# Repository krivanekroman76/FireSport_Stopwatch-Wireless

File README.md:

# FireSport Stopwatch Wireless

A DIY wireless stopwatch for FireSport training and running competitions. The system starts timing from a base station and stops when a target sensor or laser gate is triggered on a wireless endpoint, that sends signal back to the base station. It is intended for courses where running long signal cables would be inconvenient, expose them to damage or cables are inconvetions.

> **Project status:** The v6 DIY hardware and firmware are nearing a first full testing version. Timing accuracy, radio range, battery life, and water resistance have not been independently measured or certified. Treat the values and environmental protection described here as design goals, not guarantees.

## System overview

- **Base station:** An ESP32-CAM module, two MAX7219-driven 7-segment displays with 8 digits each, operator buttons, and a buzzer. The displays show the first two lanes; times from lanes 3 and 4 are available to a connected PC.
- **Endpoints:** ESP32-CAM modules with a sensor input and transistor-switched outputs for a 3 W LED and active piezoelectric buzzer. The base assigns each endpoint to a lane and segment.
- **Wireless link:** ESP-NOW, with no router or internet connection required.
- **Sensors:** Magnetic target switches or laser-gate receivers, depending on the course setup. The endpoint firmware is shared across endpoints.
- **Power:** Battery powered; the current design uses 2-cell (2S) Li-ion packs. Battery monitoring and practical runtime testing are still in progress.

The base supports **1–4 lanes**. The current firmware supports **multiple segments (up to 9) for a single lane**; multi-segment timing across several lanes is not currently supported. The physical base display shows two lanes, with additional lane results sent to the PC interface.

## How a run works

1. The operator starts the stopwatch with the base's **START** button.
2. Endpoint sensor events are sent to the base over ESP-NOW. Events are acknowledged and retried until received.
3. The base records the stop time (and segment split times when configured), updates the displays, and reports results over USB serial for PC software.
4. The base's **RESTART** button resets a run. Holding it also displays available battery readings.

The endpoint's LED gives visual feedback when a sensor event is being sent and when it has been acknowledged. Endpoint and base buzzer behavior can be configured at the base.

## V6 DIY hardware

### Base station

The base is not intended to be submerged. Its enclosure is designed to offer some splash resistance, with particular care needed around the three operator buttons, the GX12 connectors (**2-pin START, 3-pin POWER, 5-pin display output**), and the panel-mounted USB-C female connector.

Design reference: [Base and endpoint enclosure](Hardware/Endpoint-BaseBox.pdf)

<!-- Add your v6 photos under photos/DIY-v6/ and update these image paths. -->

[More base photos: all sides and connector details](photos/DIY-v6/base-details/)

### Endpoints

Each endpoint has one sensor input. The magnetic-switch setup is intended for two target lines; laser-gate setups can use one to four lanes, with up to nine segments on a single lane in the current firmware. Assign each endpoint to its lane and segment during base setup.

The endpoint enclosure design is described in the [base and endpoint enclosure document](Hardware/Endpoint-BaseBox.pdf). Protect the GX12 3-pin connections carefully when assembling the endpoint; the enclosure and connectors should not be assumed waterproof.

[More endpoint photos: all sides and connector details](photos/DIY-v6/endpoint-details/)

### Signal box

The separate signal box connects through a GX12 3-pin connector and carries common **+BATT**, a **3 W LED**, and an **active piezoelectric buzzer**. The LED and buzzer need only +BATT and GND at the signal box; they are switched by transistors in the endpoint. The signal box is designed to resist splashing, but its water resistance has not been verified and should not be treated as a waterproof rating.

Design reference: [Signal box](Hardware/SignalBox.pdf)

### System photos

## Firmware

The v6 Arduino sketches are in [`Codes/Hardware_codes/Base_v6`](Codes/Hardware_codes/Base_v6) and [`Codes/Hardware_codes/Endpoint_v6`](Codes/Hardware_codes/Endpoint_v6). Use the matching v6 firmware on the base and every endpoint.

Both sketches use a shared `protocol.h` for ESP-NOW message IDs, event acknowledgements, configuration, and battery messages. The two copies must remain identical. Each sketch also includes a local `config.h` for shared radio settings; provide the same settings to the base and endpoints and do not publish private keys.

The endpoint uses GPIO 16 for its sensor, which conflicts with ESP32-CAM PSRAM; disable PSRAM in the Arduino board settings as noted in the endpoint sketch. GPIO 13 is used for endpoint battery measurement. Because it is an ADC2 pin, measurement requires the radio/Wi-Fi to pause; reliable endpoint battery measurement is still being refined.

The base supports setup and endpoint pairing from its buttons, battery status display, serial commands, and USB serial output for PC integration. See the comments at the top of each sketch for the current pin assignments, setup flow, commands, and serial message formats.

## Wireless range and testing

The intended operating range is approximately **100–1000 m in favorable conditions**, depending on line of sight, interference, antenna placement, and ESP-NOW coverage. This range has not yet been validated in field testing. Relays may be explored in the future for longer courses such as marathons.

Before relying on the stopwatch in a competition, test the complete setup on the intended course. In particular, verify event reception and timing, endpoint assignment, battery readings and runtime, radio range, and enclosure resistance to the expected weather. This is a DIY project and is not a certified timing instrument.

## Project history

The project began with Arduino Nano boards and nRF24L01 radios. It later moved to ESP8266 and ESP-NOW, and then to ESP32-CAM modules to gain more processing speed and usable pins for the evolving design. The v6 base and endpoint firmware use ESP-NOW and the shared `protocol.h` message protocol.

## Contact and customization

Questions, orders, or requests for a specialized configuration can be discussed by email: [krivanekroman76@gmail.com](mailto:krivanekroman76@gmail.com).

## License

See the repository's [LICENSE](LICENSE) for the applicable license terms.

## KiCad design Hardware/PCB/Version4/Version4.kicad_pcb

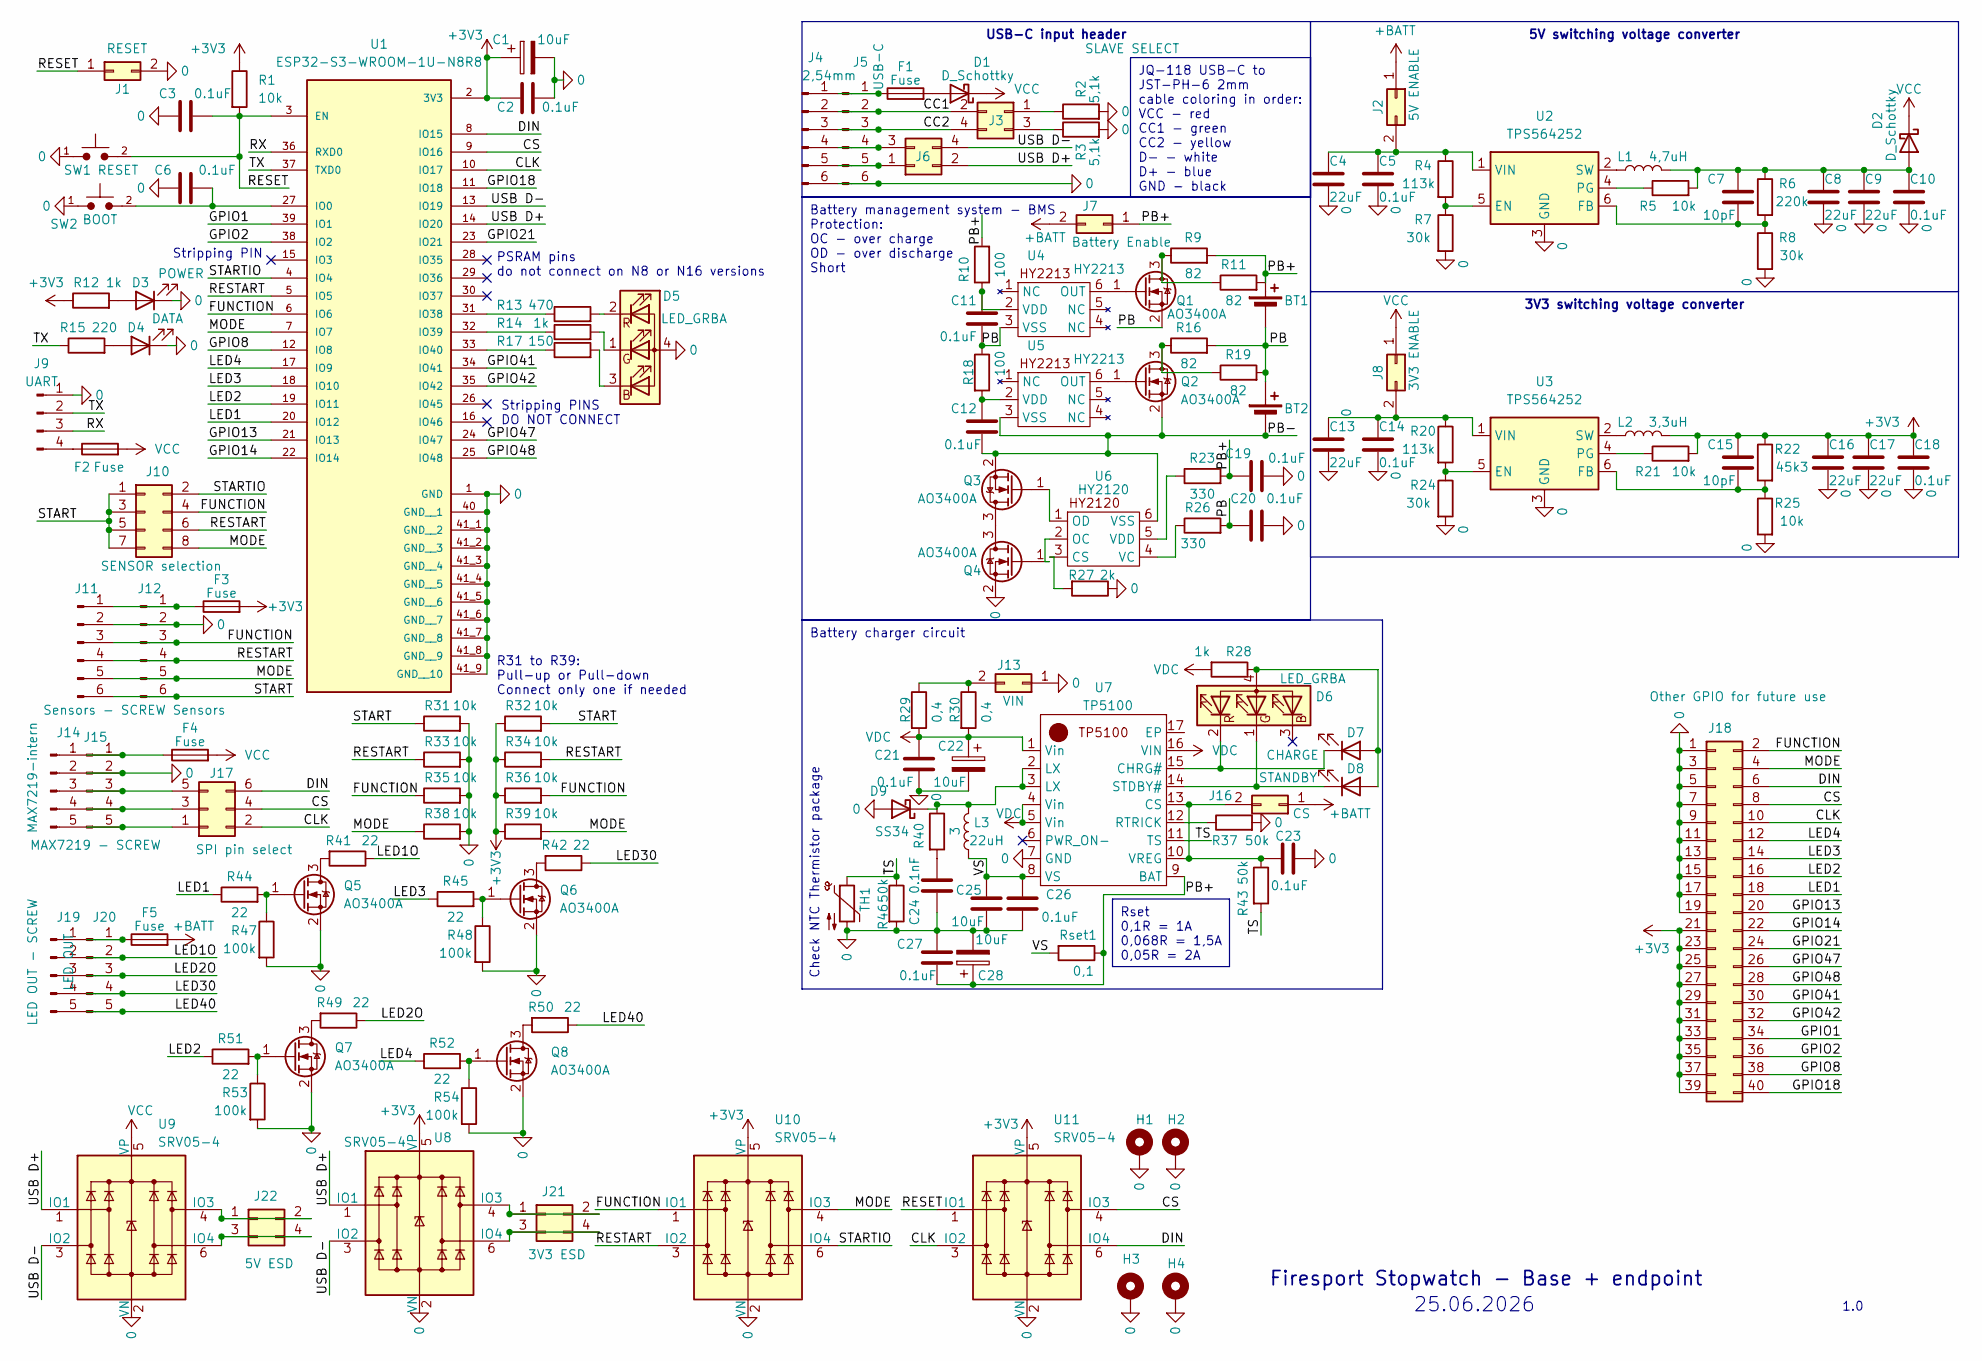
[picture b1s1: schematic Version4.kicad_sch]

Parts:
BT1, BT2: Battery_Cell; BatteryHolder_MPD_BH-18650-PC2
C1, C22, C28: 10uF; CP_Radial_D5.0mm_P2.50mm
C2, C3, C5, C6, C10, C11, C12, C14, C18, C19, C20, C21, C23, C26, C27: 0.1uF; CP_EIA-3216-18_Kemet-A_Pad1.58x1.35mm_HandSolder
C4, C8, C9, C13, C16, C17: 22uF; CP_EIA-3216-18_Kemet-A_Pad1.58x1.35mm_HandSolder
C7, C15: 10pF; CP_EIA-3216-18_Kemet-A_Pad1.58x1.35mm_HandSolder
C24: 0.1nF; CP_EIA-3216-18_Kemet-A_Pad1.58x1.35mm_HandSolder
C25: 10uF; CP_EIA-3216-18_Kemet-A_Pad1.58x1.35mm_HandSolder
D1, D2: D_Schottky; D_SMA_Handsoldering
D3: POWER; LED_1206_3216Metric_Pad1.42x1.75mm_HandSolder
D4: DATA; LED_1206_3216Metric_Pad1.42x1.75mm_HandSolder
D5, D6: LED_GRBA; LED_D5.0mm-4_RGB_Wide_Pins
D7: CHARGE; LED_1206_3216Metric_Pad1.42x1.75mm_HandSolder
D8: STANDBY; LED_1206_3216Metric_Pad1.42x1.75mm_HandSolder
D9: SS34; D_SMA
F1, F2, F3, F4, F5: Fuse; Fuse_1206_3216Metric_Pad1.42x1.75mm_HandSolder
H1, H2, H3, H4: MountingHole_Pad; MountingHole_3.2mm_M3_DIN965_Pad_TopBottom
J1: RESET; PinHeader_2x01_P2.54mm_Vertical
J2: 5V ENABLE; PinHeader_2x01_P2.54mm_Vertical
J3: SLAVE SELECT; PinHeader_2x02_P2.54mm_Vertical
J4: 2,54mm; PinHeader_1x06_P2.54mm_Vertical
J5: USB-C; JST_PH_B6B-PH-K_1x06_P2.00mm_Vertical
J6: USB data lines; PinHeader_2x02_P2.54mm_Vertical
J7: Battery Enable; PinHeader_2x01_P2.54mm_Vertical
J8: 3V3 ENABLE; PinHeader_2x01_P2.54mm_Vertical
J9: UART; PinHeader_1x04_P2.54mm_Vertical
J10: SENSOR selection; PinHeader_2x04_P2.54mm_Vertical
J11: Sensors - SCREW; TerminalBlock_bornier-6_P5.08mm
J12: Sensors; PinHeader_1x06_P2.54mm_Vertical
J13: VIN; PinHeader_2x01_P2.54mm_Vertical
J14: MAX7219-intern; PinHeader_1x05_P2.54mm_Vertical
J15: MAX7219 - SCREW; TerminalBlock_bornier-5_P5.08mm
J16: CS; PinHeader_2x01_P2.54mm_Vertical
J17: SPI pin select; PinHeader_2x03_P2.54mm_Vertical
J18: Other GPIO for future use; PinHeader_2x20_P2.54mm_Vertical
J19: LED OUT - SCREW; TerminalBlock_bornier-5_P5.08mm
J20: LED OUT; PinHeader_1x05_P2.54mm_Vertical
J21: 3V3 ESD; PinHeader_2x02_P2.54mm_Vertical
J22: 5V ESD; PinHeader_2x02_P2.54mm_Vertical
L1: 4,7uH; L_7.3x7.3_H3.5
L2: 3,3uH; L_10.4x10.4_H4.8
L3: 22uH; L_7.3x7.3_H3.5
Q1, Q2, Q3, Q4, Q5, Q6, Q7, Q8: AO3400A; SOT-23
R1, R5, R21, R25, R31, R32, R33, R34, R35, R36, R38, R39: 10k; R_1206_3216Metric_Pad1.30x1.75mm_HandSolder
R2, R3: 5,1k; R_1206_3216Metric_Pad1.30x1.75mm_HandSolder
R4, R20: 113k; R_1206_3216Metric_Pad1.30x1.75mm_HandSolder
R6: 220k; R_1206_3216Metric_Pad1.30x1.75mm_HandSolder
R7, R8, R24: 30k; R_1206_3216Metric_Pad1.30x1.75mm_HandSolder
R9, R11, R16, R19: 82; R_1206_3216Metric_Pad1.30x1.75mm_HandSolder
R10, R18: 100; R_1206_3216Metric_Pad1.30x1.75mm_HandSolder
R12, R14, R28: 1k; R_1206_3216Metric_Pad1.30x1.75mm_HandSolder
R13: 470; R_1206_3216Metric_Pad1.30x1.75mm_HandSolder
R15: 220; R_1206_3216Metric_Pad1.30x1.75mm_HandSolder
R17: 150; R_1206_3216Metric_Pad1.30x1.75mm_HandSolder
R22: 45k3; R_1206_3216Metric_Pad1.30x1.75mm_HandSolder
R23, R26: 330; R_1206_3216Metric_Pad1.30x1.75mm_HandSolder
R27: 2k; R_1206_3216Metric_Pad1.30x1.75mm_HandSolder
R29, R30: 0,4; R_1206_3216Metric_Pad1.30x1.75mm_HandSolder
R37, R43, R46: 50k; R_1206_3216Metric_Pad1.30x1.75mm_HandSolder
R40: 3; R_1206_3216Metric_Pad1.30x1.75mm_HandSolder
R41, R42, R44, R45, R49, R50, R51, R52: 22; R_1206_3216Metric_Pad1.30x1.75mm_HandSolder
R47, R48, R53, R54: 100k; R_1206_3216Metric_Pad1.30x1.75mm_HandSolder
Rset1: 0,1; R_1206_3216Metric_Pad1.30x1.75mm_HandSolder
SW1: RESET; SW_Tactile_SPST_NO_Straight_CK_PTS636Sx25SMTRLFS
SW2: BOOT; SW_Tactile_SPST_NO_Straight_CK_PTS636Sx25SMTRLFS
TH1: Thermistor_NTC; PinHeader_1x02_P2.54mm_Vertical
U1: ESP32-S3-WROOM-1U-N8R8; XCVR_ESP32-S3-WROOM-1U-N8R8; PARTREV v1.1
U2, U3: TPS564252; SOT-23-6_Handsoldering
U4, U5: HY2213; SOT-23-6_Handsoldering
U6: HY2120; SOT-23-6_Handsoldering
U7: TP5100; QFN-16-1EP_5x5mm_P0.8mm_EP2.7x2.7mm
U8, U9, U10, U11: SRV05-4; SOT-23-6

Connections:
0: C1.2, C2.2, C3.1, C4.1, C5.1, C6.1, C8.1, C9.1, C10.1, C13.1, C14.1, C16.1, C17.1, C18.1, C19.1, C20.2, C21.2, C22.2, C23.2, C24.1, C25.1, C26.1, C27.1, C28.2, D3.1 (K), D4.1 (K), D5.4 (A), D9.2 (A), H1.1, H2.1, H3.1, H4.1, J1.2, J4.6, J5.6, J9.1, J11.2, J12.2, J13.1, J14.2, J15.2, J18.1, J18.3, J18.5, J18.7, J18.9, J18.11, J18.13, J18.15, J18.17, J18.19, Q4.2 (S), Q5.2 (S), Q6.2 (S), Q7.2 (S), Q8.2 (S), R2.2, R3.2, R7.2, R8.2, R24.2, R25.2, R27.1, R31.2, R33.2, R35.2, R37.2, R38.2, R46.2, R47.2, R48.2, R53.2, R54.2, SW1.1, SW2.1, TH1.2, U1.1 (GND), U1.40 (GND__1), U1.41_1 (GND__2), U1.41_2 (GND__3), U1.41_3 (GND__4), U1.41_4 (GND__5), U1.41_5 (GND__6), U1.41_6 (GND__7), U1.41_7 (GND__8), U1.41_8 (GND__9), U1.41_9 (GND__10), U2.3 (GND), U3.3 (GND), U7.7 (GND), U8.2 (VN), U9.2 (VN), U10.2 (VN), U11.2 (VN)
+3V3: C1.1, C2.1, C15.2, C16.2, C17.2, C18.2, F3.2, J18.21, J18.23, J18.25, J18.27, J18.29, J18.31, J18.33, J18.35, J18.37, J18.39, L2.1, R1.1, R12.1, R21.2, R22.1, R32.1, R34.1, R36.1, R39.1, U1.2 (3V3), U8.5 (VP), U10.5 (VP), U11.5 (VP)
+BATT: F5.2, J2.1, J7.2, J16.1
/CC1: J3.2, J4.2, J5.2
/CC2: J3.4, J4.3, J5.3
/CLK: J17.2, J18.10, U1.10 (IO17), U11.3 (IO2)
/CS: J17.4, J18.8, U1.9 (IO16), U11.4 (IO3)
/DIN: J17.6, J18.6, U1.8 (IO15), U11.6 (IO4)
/FUNCTION: J10.4, J11.3, J12.3, J18.2, R35.1, R36.2, U1.6 (IO6), U10.1 (IO1)
/GPIO1: J18.34, U1.39 (IO1)
/GPIO2: J18.36, U1.38 (IO2)
/GPIO8: J18.38, U1.12 (IO8)
/GPIO13: J18.20, U1.21 (IO13)
/GPIO14: J18.22, U1.22 (IO14)
/GPIO18: J18.40, U1.11 (IO18)
/GPIO21: J18.24, U1.23 (IO21)
/GPIO41: J18.30, U1.34 (IO41)
/GPIO42: J18.32, U1.35 (IO42)
/GPIO47: J18.26, U1.24 (IO47)
/GPIO48: J18.28, U1.25 (IO48)
/LED1: J18.18, R44.1, U1.20 (IO12)
/LED1O: J19.2, J20.2, R41.1
/LED2: J18.16, R51.1, U1.19 (IO11)
/LED2O: J19.3, J20.3, R49.1
/LED3: J18.14, R45.1, U1.18 (IO10)
/LED4: J18.12, R52.1, U1.17 (IO9)
/LED30: J19.4, J20.4, R42.1
/LED40: J19.5, J20.5, R50.1
/MODE: J10.8, J11.5, J12.5, J18.4, R38.1, R39.2, U1.7 (IO7), U10.4 (IO3)
/PB: BT1.2 (-), BT2.1 (+), C11.2, C20.1, Q1.2 (S), R16.2, R18.1, R19.2, R26.2, U4.3 (VSS)
/PB+: BT1.1 (+), C19.2, C27.2, C28.1, J7.1, R9.2, R10.2, R11.2, R23.2, Rset1.1, U7.9 (BAT)
/PB-: BT2.2 (-), C12.2, Q2.2 (S), Q3.2 (S), U5.3 (VSS), U6.6 (VSS)
/RESET: C3.2, J1.1, R1.2, SW1.2, U1.3 (EN), U11.1 (IO1)
/RESTART: J10.6, J11.4, J12.4, R33.1, R34.2, U1.5 (IO5), U10.3 (IO2)
/RX: J9.3, U1.36 (RXD0)
/START: J10.1, J10.3, J10.5, J10.7, J11.6, J12.6, R31.1, R32.2
/STARTIO: J10.2, U1.4 (IO4), U10.6 (IO4)
/TS: R43.2, R46.1, TH1.1, U7.11 (TS)
/TX: J9.2, R15.1, U1.37 (TXD0)
/USB D+: J6.2, U1.14 (IO20), U8.1 (IO1), U9.1 (IO1)
/USB D-: J6.4, U1.13 (IO19), U8.3 (IO2), U9.3 (IO2)
/VS: C25.2, C26.2, L3.1, Rset1.2, U7.8 (VS)
unnamed: C24.2, R40.2
unnamed: D1.2 (A), F1.2
unnamed: C7.2, C8.2, C9.2, C10.2, D2.2 (A), L1.1, R5.2, R6.1
unnamed: D3.2 (A), R12.2
unnamed: D4.2 (A), R15.2
unnamed: D5.3 (BK), R17.2
unnamed: D5.1 (GK), R14.2
unnamed: D5.2 (RK), R13.2
unnamed: D6.4 (A), D7.2 (A), D8.2 (A), R28.1
unnamed: D6.1 (GK), D8.1 (K), U7.14 (STDBY#)
unnamed: D6.2 (RK), D7.1 (K), U7.15 (CHRG#)
unnamed: D9.1 (K), L3.2, R40.1, U7.2 (LX), U7.3 (LX)
unnamed: C4.2, C5.2, J2.2, R4.1, U2.1 (VIN)
unnamed: J3.1, R2.1
unnamed: J3.3, R3.1
unnamed: F1.1, J4.1, J5.1
unnamed: J4.4, J5.4, J6.3
unnamed: J4.5, J5.5, J6.1
unnamed: C13.2, C14.2, J8.2, R20.1, U3.1 (VIN)
unnamed: F2.1, J9.4
unnamed: F3.1, J11.1, J12.1
unnamed: J13.2, R29.1, R30.1
unnamed: F4.1, J14.1, J15.1
unnamed: J14.3, J15.3, J17.5
unnamed: J14.4, J15.4, J17.3
unnamed: J14.5, J15.5, J17.1
unnamed: C23.1, J16.2, R43.1, U7.10 (VREG), U7.13 (CS)
unnamed: F5.1, J19.1, J20.1
unnamed: J21.1, J21.2, U8.4 (IO3)
unnamed: J21.3, J21.4, U8.6 (IO4)
unnamed: J22.1, J22.2, U9.4 (IO3)
unnamed: J22.3, J22.4, U9.6 (IO4)
unnamed: Q1.3 (D), R9.1, R11.1
unnamed: Q1.1 (G), U4.6 (OUT)
unnamed: Q2.3 (D), R16.1, R19.1
unnamed: Q2.1 (G), U5.6 (OUT)
unnamed: Q3.3 (D), Q4.3 (D)
unnamed: Q3.1 (G), U6.1 (OD)
unnamed: Q4.1 (G), U6.2 (OC)
unnamed: Q5.3 (D), R41.2
unnamed: Q5.1 (G), R44.2, R47.1
unnamed: Q6.3 (D), R42.2
unnamed: Q6.1 (G), R45.2, R48.1
unnamed: Q7.3 (D), R49.2
unnamed: Q7.1 (G), R51.2, R53.1
unnamed: Q8.3 (D), R50.2
unnamed: Q8.1 (G), R52.2, R54.1
unnamed: C6.2, SW2.2, U1.27 (IO0)
unnamed: R13.1, U1.31 (IO38)
unnamed: R14.1, U1.32 (IO39)
unnamed: R17.1, U1.33 (IO40)
unnamed: R4.2, R7.1, U2.5 (EN)
unnamed: C7.1, R6.2, R8.1, U2.6 (FB)
unnamed: R5.1, U2.4 (PG)
unnamed: L1.2, U2.2 (SW)
unnamed: R20.2, R24.1, U3.5 (EN)
unnamed: C15.1, R22.2, R25.1, U3.6 (FB)
unnamed: R21.1, U3.4 (PG)
unnamed: L2.2, U3.2 (SW)
unnamed: C11.1, R10.1, U4.2 (VDD)
unnamed: C12.1, R18.2, U5.2 (VDD)
unnamed: R27.2, U6.3 (CS)
unnamed: R26.1, U6.4 (VC)
unnamed: R23.1, U6.5 (VDD)
unnamed: R37.1, U7.12 (RTRICK)
VCC: D1.1 (K), D2.1 (K), F2.2, F4.2, J8.1, U9.5 (VP)
VDC: C21.1, C22.1, R28.2, R29.2, R30.2, U7.1 (Vin), U7.4 (Vin), U7.5 (Vin), U7.16 (VIN)

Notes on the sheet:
5V switching voltage converter
USB-C input header
JQ-118 USB-C to JST-PH-6 2mm cable coloring in order: VCC - red CC1 - green CC2 - yellow D- - white D+ - blue GND - black
3V3 switching voltage converter
Battery management system - BMS Protection: OC - over charge OD - over discharge Short
Rset 0,1R = 1A 0,068R = 1,5A 0,05R = 2A
Battery charger circuit
25.06.2026
Firesport Stopwatch - Base + endpoint
Stripping PIN
1.0
R31 to R39: Pull-up or Pull-down Connect only one if needed
PSRAM pins do not connect on N8 or N16 versions
Check NTC Thermistor package
Stripping PINS DO NOT CONNECT

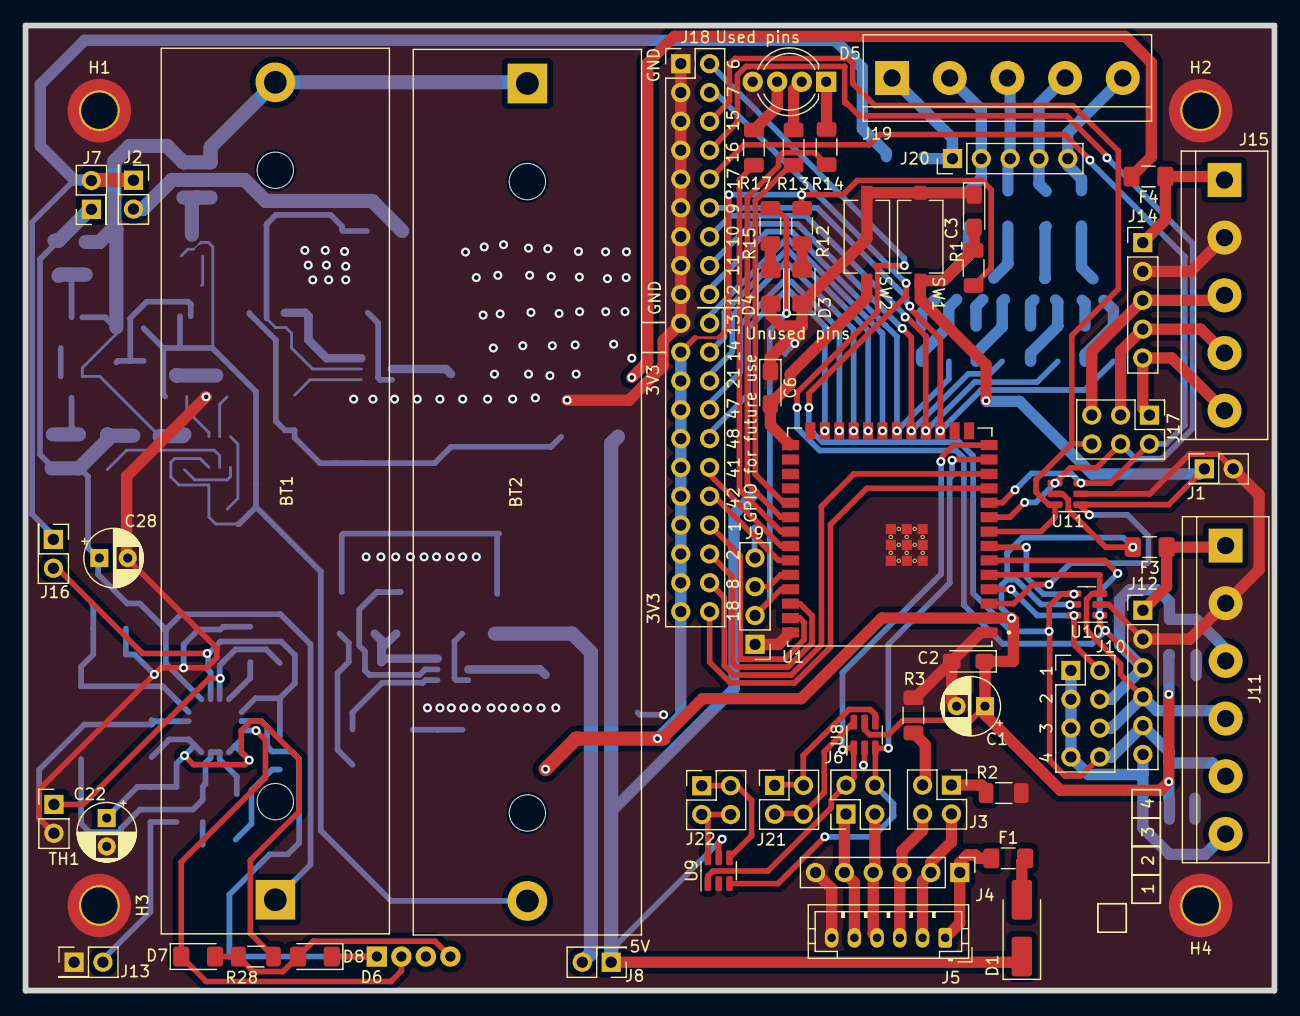
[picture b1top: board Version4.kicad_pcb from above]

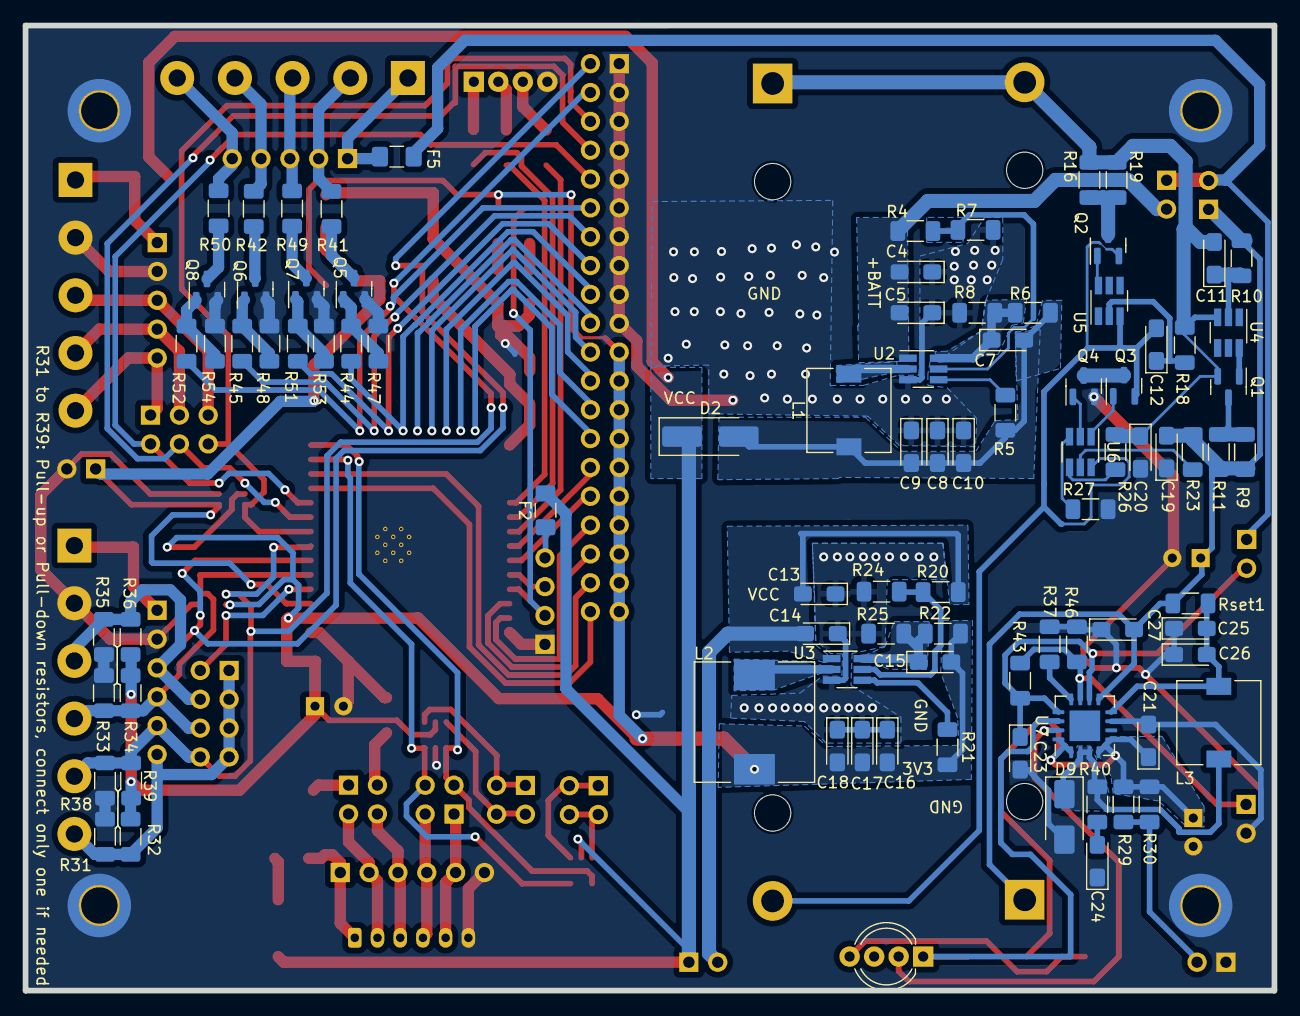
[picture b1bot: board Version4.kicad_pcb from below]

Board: 2 copper layers, 110.0 x 85.0 mm, 150 parts (90 on the bottom side), 109 nets.

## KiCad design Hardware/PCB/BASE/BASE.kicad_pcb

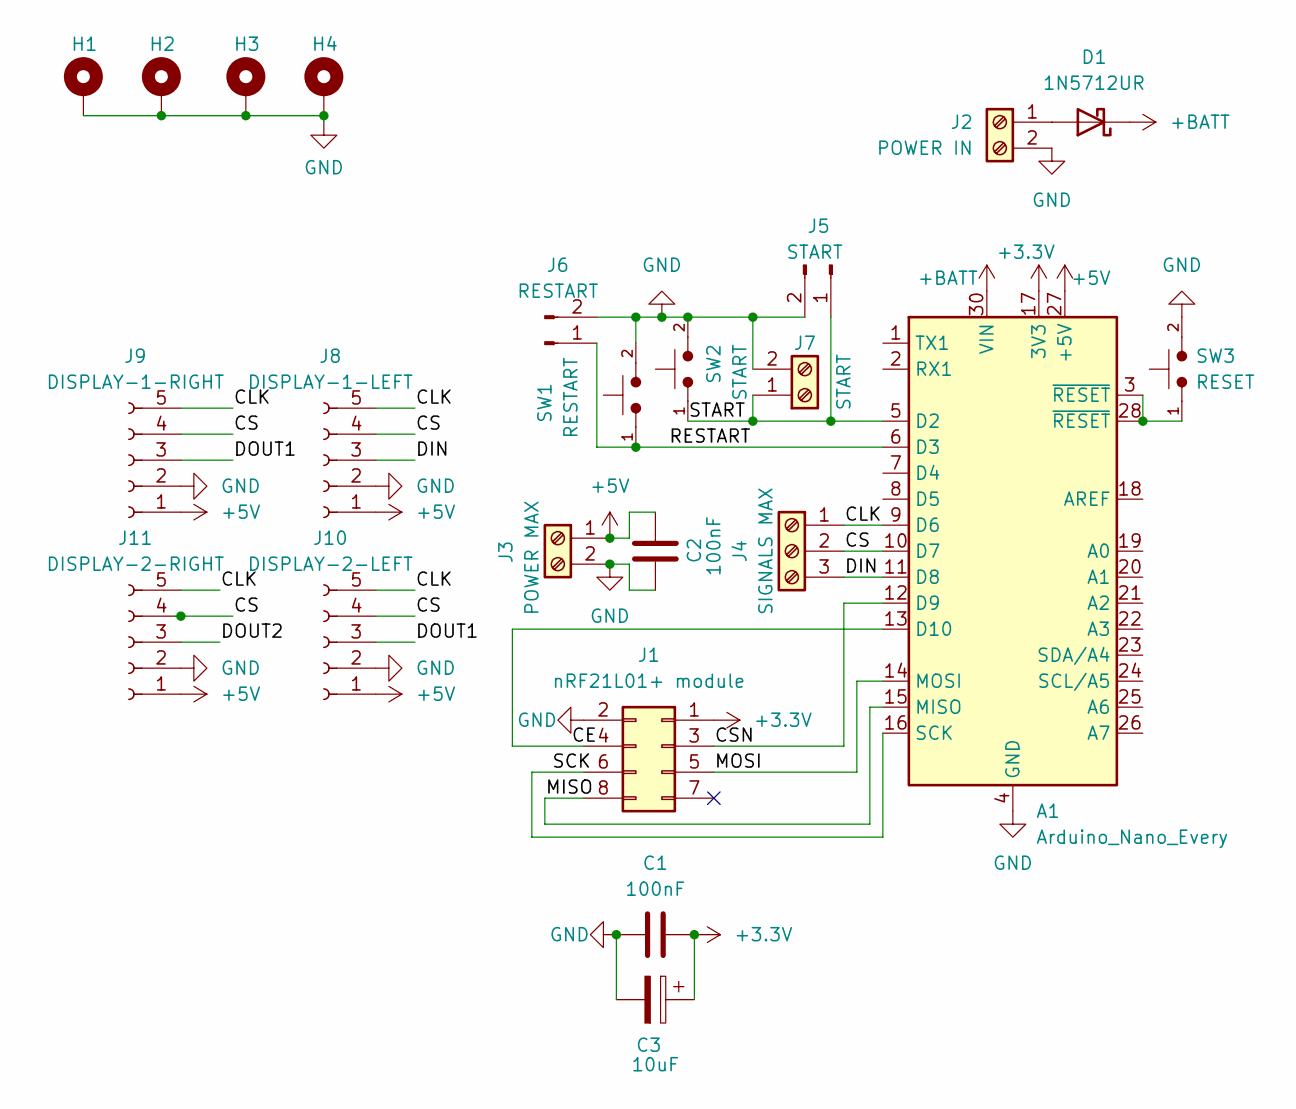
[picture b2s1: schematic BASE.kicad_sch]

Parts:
A1: Arduino_Nano_Every; Arduino_Nano
C1, C2: 100nF; C_1206_3216Metric_Pad1.33x1.80mm_HandSolder
C3: 10uF; CP_Radial_D10.0mm_P5.00mm
D1: 1N5712UR; D_MELF
H1, H2, H3, H4: MountingHole_Pad; MountingHole_3.2mm_M3_ISO7380_Pad_TopBottom
J1: nRF21L01+ module; PinSocket_2x04_P2.54mm_Vertical
J2: POWER IN; TerminalBlock_Altech_AK300-2_P5.00mm
J3: POWER MAX; TerminalBlock_Altech_AK300-2_P5.00mm
J4: SIGNALS MAX; TerminalBlock_Altech_AK300-3_P5.00mm
J5: START; PinSocket_1x02_P2.54mm_Vertical
J6: RESTART; PinSocket_1x02_P2.54mm_Vertical
J7: START; TerminalBlock_Altech_AK300-2_P5.00mm
J8: DISPLAY-1-LEFT; PinSocket_1x05_P2.54mm_Vertical
J9: DISPLAY-1-RIGHT; PinSocket_1x05_P2.54mm_Vertical
J10: DISPLAY-2-LEFT; PinSocket_1x05_P2.54mm_Vertical
J11: DISPLAY-2-RIGHT; PinSocket_1x05_P2.54mm_Vertical
SW1: RESTART; SW_PUSH_6mm
SW2: START; SW_PUSH_6mm
SW3: RESET; SW_PUSH_6mm

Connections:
+3.3V: A1.17 (3V3), C1.2, C3.1, J1.1
+5V: A1.27 (+5V), C2.1, J3.1, J8.1, J9.1, J10.1, J11.1
+BATT: A1.30 (VIN), D1.1 (K)
/CE: A1.13 (D10), J1.4
/CLK: A1.9 (D6), J4.1, J8.5, J9.5, J10.5, J11.5
/CS: A1.10 (D7), J4.2, J8.4, J9.4, J10.4, J11.4
/CSN: A1.12 (D9), J1.3
/DIN: A1.11 (D8), J4.3, J8.3
/DOUT1: J9.3, J10.3
/DOUT2: J11.3
/MISO: A1.15 (MISO), J1.8
/MOSI: A1.14 (MOSI), J1.5
/RESTART: A1.6 (D3), J6.1, SW1.1
/SCK: A1.16 (SCK), J1.6
/START: A1.5 (D2), J5.1, J7.1, SW2.1
GND: A1.4 (GND), A1.29 (GND), C1.1, C2.2, C3.2, H1.1, H2.1, H3.1, H4.1, J1.2, J2.2, J3.2, J5.2, J6.2, J7.2, J8.2, J9.2, J10.2, J11.2, SW1.2, SW2.2, SW3.2
unnamed: A1.3 (~RESET), A1.28 (~RESET), SW3.1
unnamed: D1.2 (A), J2.1

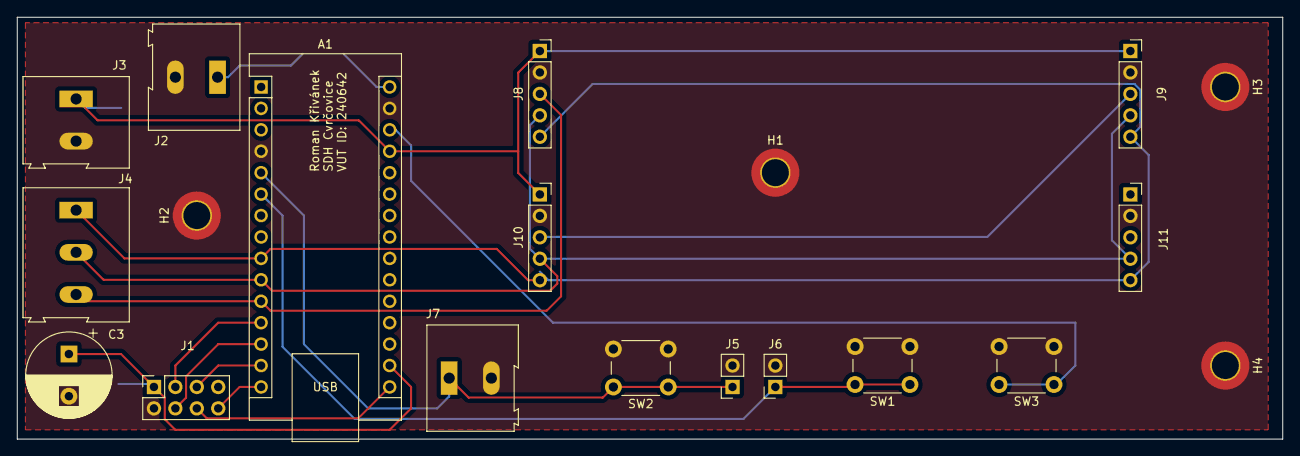
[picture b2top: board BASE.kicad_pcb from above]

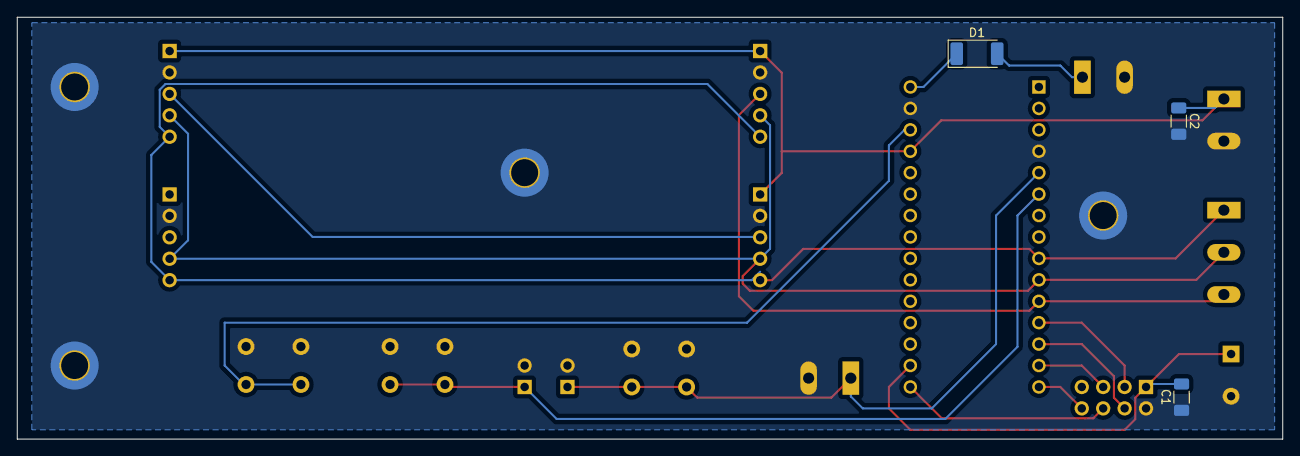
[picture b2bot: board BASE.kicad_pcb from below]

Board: 2 copper layers, 150.0 x 50.0 mm, 23 parts (3 on the bottom side), 17 nets.

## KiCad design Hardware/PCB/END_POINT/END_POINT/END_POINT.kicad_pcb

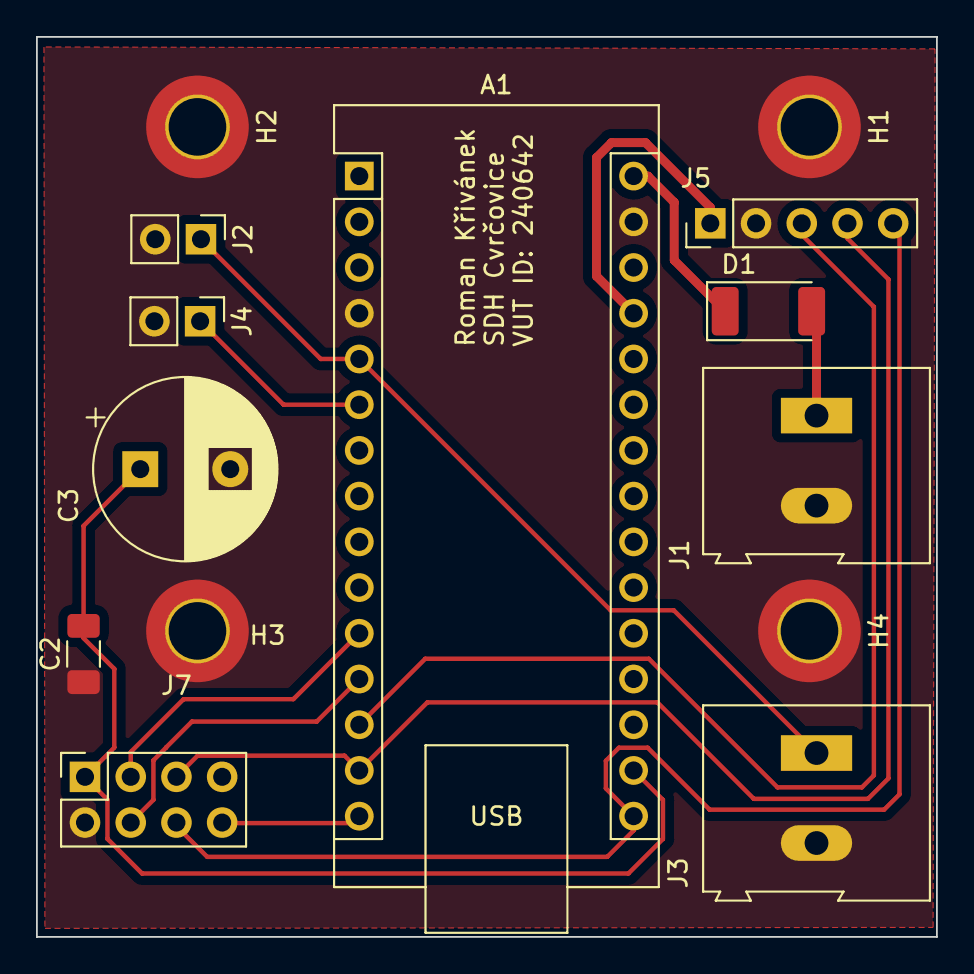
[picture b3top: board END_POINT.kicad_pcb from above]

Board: 2 copper layers, 50.0 x 50.0 mm, 14 parts (0 on the bottom side), 13 nets.

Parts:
A1: Arduino_Nano_Every; Arduino_Nano
C2: 100nF; C_1206_3216Metric_Pad1.33x1.80mm_HandSolder
C3: 10uF; CP_Radial_D10.0mm_P5.00mm
D1: 1N5712UR; D_MELF
H1, H2, H3, H4: MountingHole_Pad; MountingHole_3.2mm_M3_ISO7380_Pad_TopBottom
J1: POWER IN; TerminalBlock_Altech_AK300-2_P5.00mm
J2: STOP; PinHeader_1x02_P2.54mm_Vertical
J3: STOP; TerminalBlock_Altech_AK300-2_P5.00mm
J4: SELECT; PinHeader_1x02_P2.54mm_Vertical
J5: Conn_01x05_Pin; PinHeader_1x05_P2.54mm_Vertical
J7: nRF21L01+ module; PinSocket_2x04_P2.54mm_Vertical

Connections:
+3.3V: A1.17 (3V3), C2.2, C3.1, J7.1
+5V: A1.27 (+5V), J5.1
+BATT: A1.30 (VIN), D1.1 (K)
/CE: A1.12 (D9), J7.4
/CS: A1.13 (D10), J5.3
/CSN: A1.11 (D8), J7.3
/MISO: A1.15 (MISO), J7.8
/MOSI: A1.14 (MOSI), J5.4, J7.5
/SCK: A1.16 (SCK), J5.5, J7.6
GND: A1.4 (GND), A1.29 (GND), C2.1, C3.2, H1.1, H2.1, H3.1, H4.1, J1.2, J2.2, J3.2, J4.2, J5.2, J7.2
unnamed: A1.5 (D2), J2.1, J3.1
unnamed: A1.6 (D3), J4.1
unnamed: D1.2 (A), J1.1

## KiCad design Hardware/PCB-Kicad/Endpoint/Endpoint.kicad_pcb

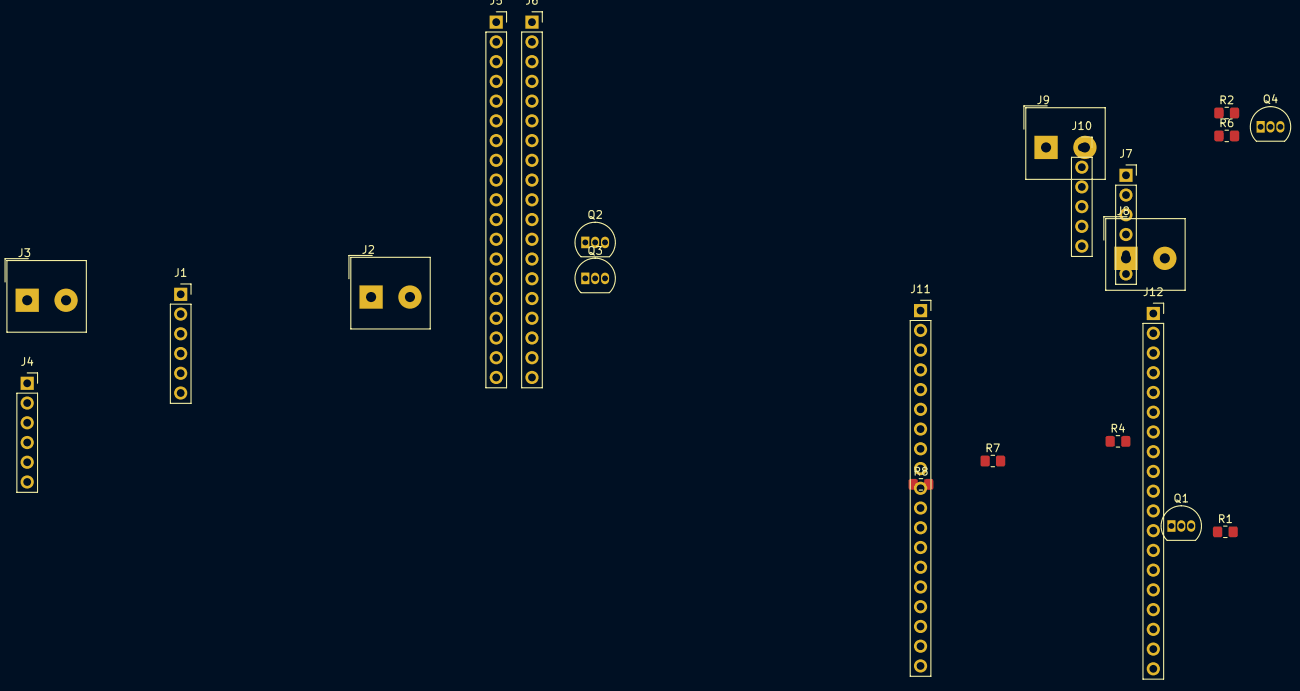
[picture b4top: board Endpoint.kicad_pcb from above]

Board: 2 copper layers, 22 parts (0 on the bottom side), 10 nets, no tracks yet.

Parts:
J1, J4, J7, J10: Conn_01x08_Socket; PinSocket_1x06_P2.54mm_Vertical
J2, J3, J8, J9: Screw_Terminal_01x02; Altech_AK100_1x02_P5.00mm
J5, J6, J11, J12: Conn_01x19_Socket; PinSocket_1x19_P2.54mm_Vertical
Q1, Q2, Q3, Q4: PN2222A; TO-92_Inline
R1, R2, R4, R6, R7, R8: 2.7; R_0805_2012Metric_Pad1.20x1.40mm_HandSolder

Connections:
/13_1: J2.2, J5.15
/13_2: J8.2, J11.15
/A11: J1.1, J1.2, Q1.3 (C), R1.2, R2.2
/A12: J7.1, J7.2, Q3.3 (C), R6.2
/A21: J1.5, J4.1, J4.4, J4.6, Q2.3 (C), R4.2
/A22: J7.5, J10.1, J10.4, J10.6, Q4.3 (C), R7.2, R8.2
/Vin1: J1.3, J1.4, J1.6, J3.1, J4.2, J4.3, J4.5, J5.19, R1.1, R2.1, R4.1
/Vin2: J7.3, J7.4, J7.6, J9.1, J10.2, J10.3, J10.5, J11.19, R6.1, R7.1, R8.1
GND1: J2.1, J3.2, J5.14, J6.1, J6.7, Q1.1 (E), Q2.1 (E)
GND2: J8.1, J9.2, J11.14, J12.1, J12.7, Q3.1 (E), Q4.1 (E)

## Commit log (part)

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2026-03-08 added python code for leaderboard application, started on PCB
2026-03-20 Flutter app commit
2026-06-19 updated files, added multiplatform and PC app for controling
